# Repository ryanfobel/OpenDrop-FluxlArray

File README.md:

## OpenDrop-FluxlArray

DMF chip compatible with the [WheelerLab fork of OpenDrop](https://github.com/ryanfobel/OpenDrop)

### Don't click on the files!

Click on the "Download ZIP" Button to the right.
Then unpack the archive.

### Open Source Digital Microfluidics Bio Lab

[OpenDrop] is a new design for an open source digital microfludics platform for research purposes. The device uses recent electro-wetting technology to control small droplets of liquids. Potential applications are lab on a chip devices for automating processes of digital biology. How ever the present design should also open the technology to other field and allow experimentation to find new applications. Including the field of art, music, games and education.

Note that this version has been forked from [v2.1](https://github.com/GaudiLabs/OpenDrop/commit/5bb955d). This repository contains the passive DMF chip (which is now detachable using a slot-connector). The high-voltage driving electronics (i.e., the microcontroller, high-voltage boost converter, and switches) are contained in a [separate repository](https://github.com/ryanfobel/OpenDrop)). This version also provides software control of the driving voltage using a digital potentiometer (controlled via i2c) and adds the capability to insert high-pass filters on each of the output channels to support bipolar AC actuation.

### License

[OpenDrop], all design files and software are licensed under a GNU GENERAL PUBLIC LICENSE
See license file in the repository.

### Contributions ###

Original design by Urs Gaudenz ([GaudiLabs](http://www.gaudi.ch)) with modifications by [Ryan Fobel](https://github.com/ryanfobel) ([Wheeler Microfluidics Lab](http://microfluidics.utoronto.ca)).

[OpenDrop]: http://www.gaudi.ch/OpenDrop/

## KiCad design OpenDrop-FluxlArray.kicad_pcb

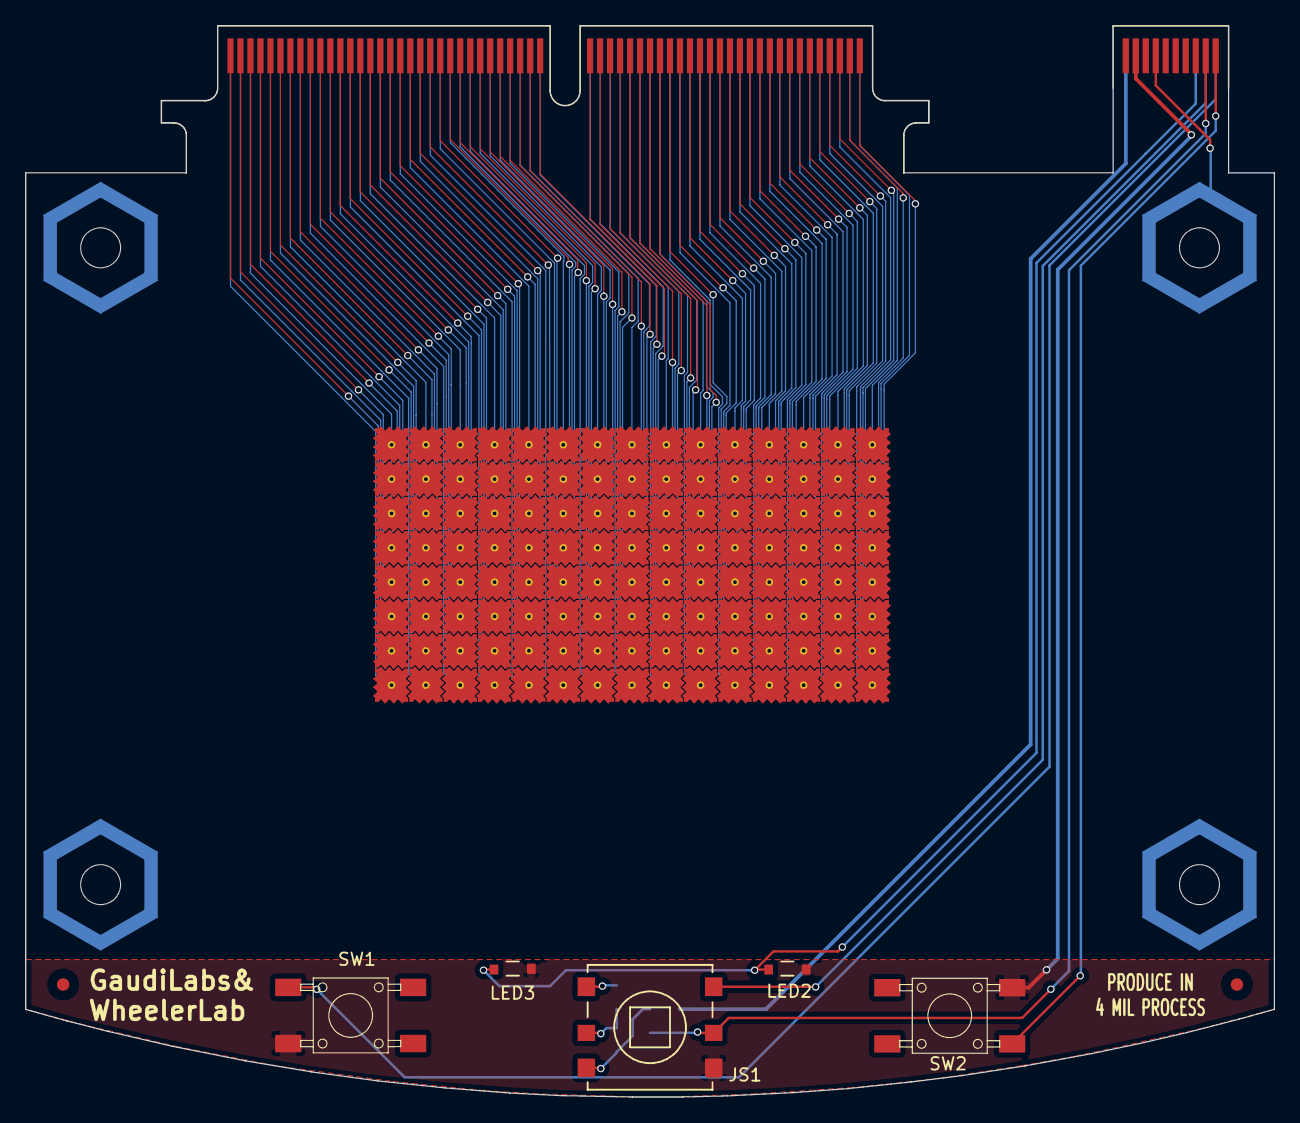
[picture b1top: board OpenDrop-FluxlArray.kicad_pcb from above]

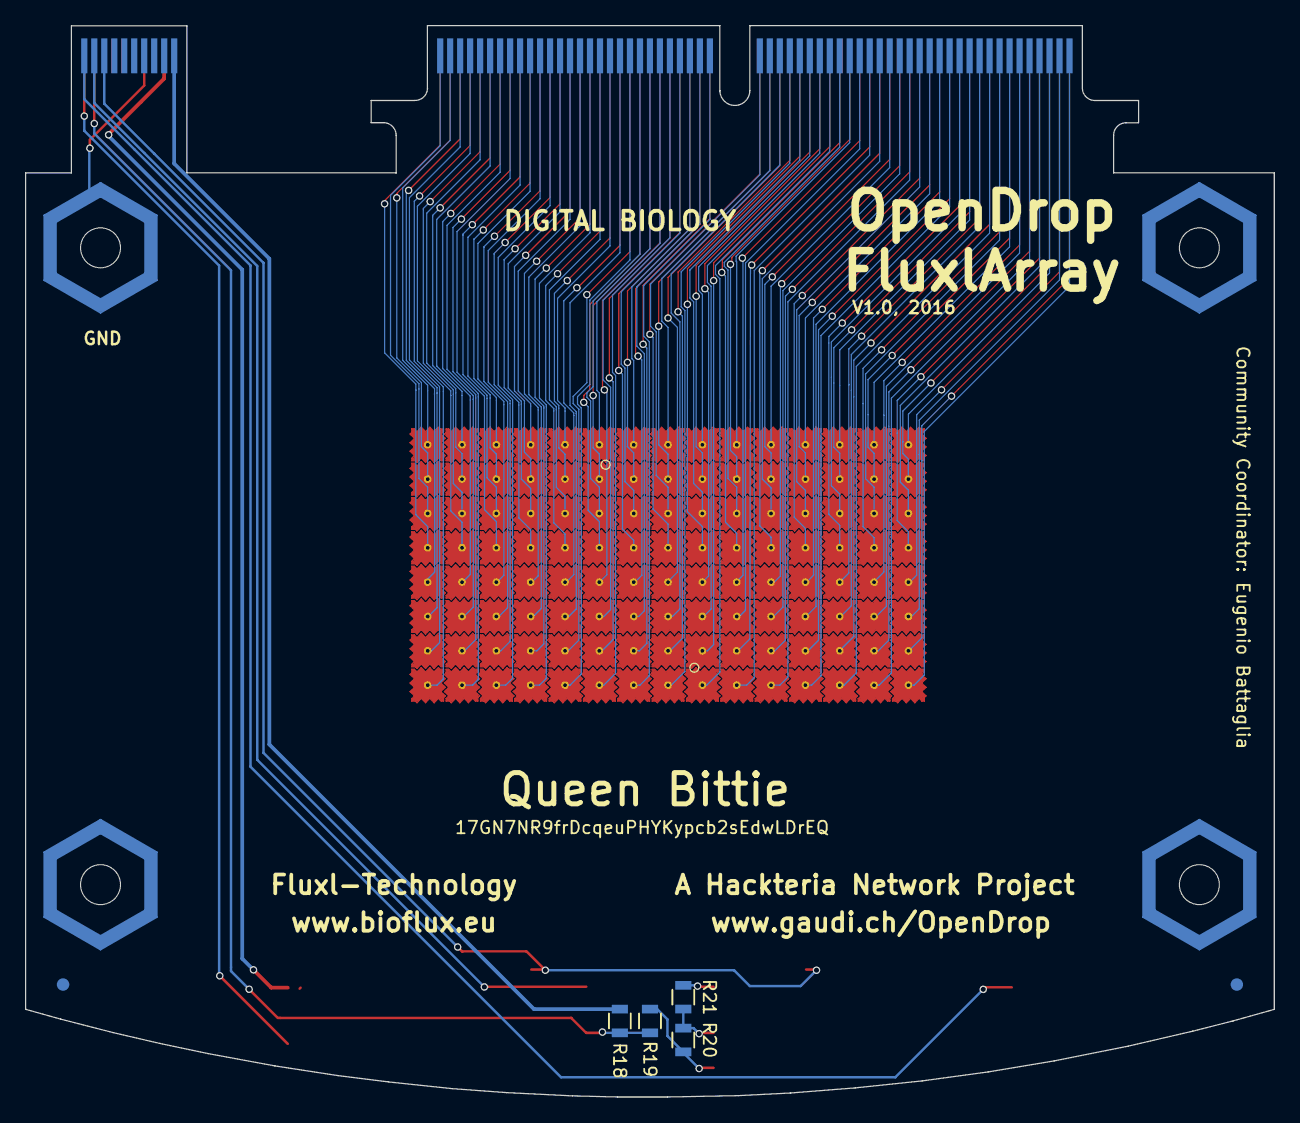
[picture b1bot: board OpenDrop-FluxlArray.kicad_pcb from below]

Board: 2 copper layers, 100.0 x 85.8 mm, 135 parts (4 on the bottom side), 130 nets.

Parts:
FLUXL1, FLUXL2, FLUXL3, FLUXL4, FLUXL5, FLUXL6, FLUXL7, FLUXL8, FLUXL9, FLUXL10, FLUXL11, FLUXL12, FLUXL13, FLUXL14, FLUXL15, FLUXL16, FLUXL17, FLUXL18, FLUXL19, FLUXL20, FLUXL21, FLUXL22, FLUXL23, FLUXL24, FLUXL25, FLUXL26, FLUXL27, FLUXL28, FLUXL29, FLUXL30, FLUXL31, FLUXL32, FLUXL33, FLUXL34, FLUXL35, FLUXL36, FLUXL37, FLUXL38, FLUXL39, FLUXL40, FLUXL41, FLUXL42, FLUXL43, FLUXL44, FLUXL45, FLUXL46, FLUXL47, FLUXL48, FLUXL49, FLUXL50, FLUXL51, FLUXL52, FLUXL53, FLUXL54, FLUXL55, FLUXL56, FLUXL57, FLUXL58, FLUXL59, FLUXL60, FLUXL61, FLUXL62, FLUXL63, FLUXL64, FLUXL65, FLUXL66, FLUXL67, FLUXL68, FLUXL69, FLUXL70, FLUXL71, FLUXL72, FLUXL73, FLUXL74, FLUXL75, FLUXL76, FLUXL77, FLUXL78, FLUXL79, FLUXL80, FLUXL81, FLUXL82, FLUXL83, FLUXL84, FLUXL85, FLUXL86, FLUXL87, FLUXL88, FLUXL89, FLUXL90, FLUXL91, FLUXL92, FLUXL93, FLUXL94, FLUXL95, FLUXL96, FLUXL97, FLUXL98, FLUXL99, FLUXL100, FLUXL101, FLUXL102, FLUXL103, FLUXL104, FLUXL105, FLUXL106, FLUXL107, FLUXL108, FLUXL109, FLUXL110, FLUXL111, FLUXL112, FLUXL113, FLUXL114, FLUXL115, FLUXL116, FLUXL117, FLUXL118, FLUXL119, FLUXL120: FX; FLUXPAD_2_75_4MIL_4_5
JS1: JoystickSMD; JoystickSMD_SKQUSeries
LED2, LED3: LED; LED_SIDE
P1: CONN_02X60; HSEC8-160-XX-X-RA-BL-MATE
P2: CONN_02X10; HSEC8-110-XX-X-RA-MATE
P13, P14, P15, P16: CONN_01X01; MountingHolePad_3x9mm
R18, R19, R20, R21: 10k; R_0805
SW1, SW2: SW_PUSH; PUSH_BUTTON_SMD

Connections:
+5V: P2.1, R18.2
GND: JS1.4, LED2.1, LED3.1, P2.4, SW1.2, SW2.2
JOY: JS1.5, P2.18, R18.1, R19.2
LED: LED2.2, LED3.2, P2.15
unnamed: FLUXL1.1, P1.1
unnamed: FLUXL2.1, P1.2
unnamed: FLUXL3.1, P1.3
unnamed: FLUXL4.1, P1.4
unnamed: FLUXL5.1, P1.8
unnamed: FLUXL6.1, P1.7
unnamed: FLUXL7.1, P1.6
unnamed: FLUXL8.1, P1.5
unnamed: FLUXL9.1, P1.9
unnamed: FLUXL10.1, P1.10
unnamed: FLUXL11.1, P1.11
unnamed: FLUXL12.1, P1.12
unnamed: FLUXL13.1, P1.16
unnamed: FLUXL14.1, P1.15
unnamed: FLUXL15.1, P1.14
unnamed: FLUXL16.1, P1.13
unnamed: FLUXL17.1, P1.17
unnamed: FLUXL18.1, P1.18
unnamed: FLUXL19.1, P1.19
unnamed: FLUXL20.1, P1.20
unnamed: FLUXL21.1, P1.24
unnamed: FLUXL22.1, P1.23
unnamed: FLUXL23.1, P1.22
unnamed: FLUXL24.1, P1.21
unnamed: FLUXL25.1, P1.25
unnamed: FLUXL26.1, P1.26
unnamed: FLUXL27.1, P1.27
unnamed: FLUXL28.1, P1.28
unnamed: FLUXL29.1, P1.32
unnamed: FLUXL30.1, P1.31
unnamed: FLUXL31.1, P1.30
unnamed: FLUXL32.1, P1.29
unnamed: FLUXL33.1, P1.33
unnamed: FLUXL34.1, P1.34
unnamed: FLUXL35.1, P1.35
unnamed: FLUXL36.1, P1.36
unnamed: FLUXL37.1, P1.40
unnamed: FLUXL38.1, P1.39
unnamed: FLUXL39.1, P1.38
unnamed: FLUXL40.1, P1.37
unnamed: FLUXL41.1, P1.41
unnamed: FLUXL42.1, P1.42
unnamed: FLUXL43.1, P1.43
unnamed: FLUXL44.1, P1.44
unnamed: FLUXL45.1, P1.48
unnamed: FLUXL46.1, P1.47
unnamed: FLUXL47.1, P1.46
unnamed: FLUXL48.1, P1.45
unnamed: FLUXL49.1, P1.49
unnamed: FLUXL50.1, P1.50
unnamed: FLUXL51.1, P1.51
unnamed: FLUXL52.1, P1.52
unnamed: FLUXL53.1, P1.56
unnamed: FLUXL54.1, P1.55
unnamed: FLUXL55.1, P1.54
unnamed: FLUXL56.1, P1.53
unnamed: FLUXL57.1, P1.57
unnamed: FLUXL58.1, P1.58
unnamed: FLUXL59.1, P1.59
unnamed: FLUXL60.1, P1.60
unnamed: FLUXL61.1, P1.64
unnamed: FLUXL62.1, P1.63
unnamed: FLUXL63.1, P1.62
unnamed: FLUXL64.1, P1.61
unnamed: FLUXL65.1, P1.65
unnamed: FLUXL66.1, P1.66
unnamed: FLUXL67.1, P1.67
unnamed: FLUXL68.1, P1.68
unnamed: FLUXL69.1, P1.72
unnamed: FLUXL70.1, P1.71
unnamed: FLUXL71.1, P1.70
unnamed: FLUXL72.1, P1.69
unnamed: FLUXL73.1, P1.73
unnamed: FLUXL74.1, P1.74
unnamed: FLUXL75.1, P1.75
unnamed: FLUXL76.1, P1.76
unnamed: FLUXL77.1, P1.80
unnamed: FLUXL78.1, P1.79
unnamed: FLUXL79.1, P1.78
unnamed: FLUXL80.1, P1.77
unnamed: FLUXL81.1, P1.81
unnamed: FLUXL82.1, P1.82
unnamed: FLUXL83.1, P1.83
unnamed: FLUXL84.1, P1.84
unnamed: FLUXL85.1, P1.88
unnamed: FLUXL86.1, P1.87
unnamed: FLUXL87.1, P1.86
unnamed: FLUXL88.1, P1.85
unnamed: FLUXL89.1, P1.89
unnamed: FLUXL90.1, P1.90
unnamed: FLUXL91.1, P1.91
unnamed: FLUXL92.1, P1.92
unnamed: FLUXL93.1, P1.96
unnamed: FLUXL94.1, P1.95
unnamed: FLUXL95.1, P1.94
unnamed: FLUXL96.1, P1.93
unnamed: FLUXL97.1, P1.97
unnamed: FLUXL98.1, P1.98
unnamed: FLUXL99.1, P1.99
unnamed: FLUXL100.1, P1.100
unnamed: FLUXL101.1, P1.104
unnamed: FLUXL102.1, P1.103
unnamed: FLUXL103.1, P1.102
unnamed: FLUXL104.1, P1.101
unnamed: FLUXL105.1, P1.105
unnamed: FLUXL106.1, P1.106
unnamed: FLUXL107.1, P1.107
unnamed: FLUXL108.1, P1.108
unnamed: FLUXL109.1, P1.112
unnamed: FLUXL110.1, P1.111
unnamed: FLUXL111.1, P1.110
unnamed: FLUXL112.1, P1.109
unnamed: FLUXL113.1, P1.113
unnamed: FLUXL114.1, P1.114
unnamed: FLUXL115.1, P1.115
unnamed: FLUXL116.1, P1.116
unnamed: FLUXL117.1, P1.120
unnamed: FLUXL118.1, P1.119
unnamed: FLUXL119.1, P1.118
unnamed: FLUXL120.1, P1.117
unnamed: JS1.1, R21.1
unnamed: JS1.2, R20.1, R21.2
unnamed: JS1.3, R19.1, R20.2
SW1: P2.19, SW1.1
SW2: P2.20, SW2.1
SW3: JS1.6, P2.17

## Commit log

2016-11-11 Initial commit
    This is a modifed version of the DMF electrode array forked from
    https://github.com/GaudiLabs/OpenDrop/commit/5bb955d. It detaches
    the passive DMF chip from the driving electronics contained in
    https://github.com/ryanfobel/OpenDrop.
2016-11-14 Bump WheelerLab library version
